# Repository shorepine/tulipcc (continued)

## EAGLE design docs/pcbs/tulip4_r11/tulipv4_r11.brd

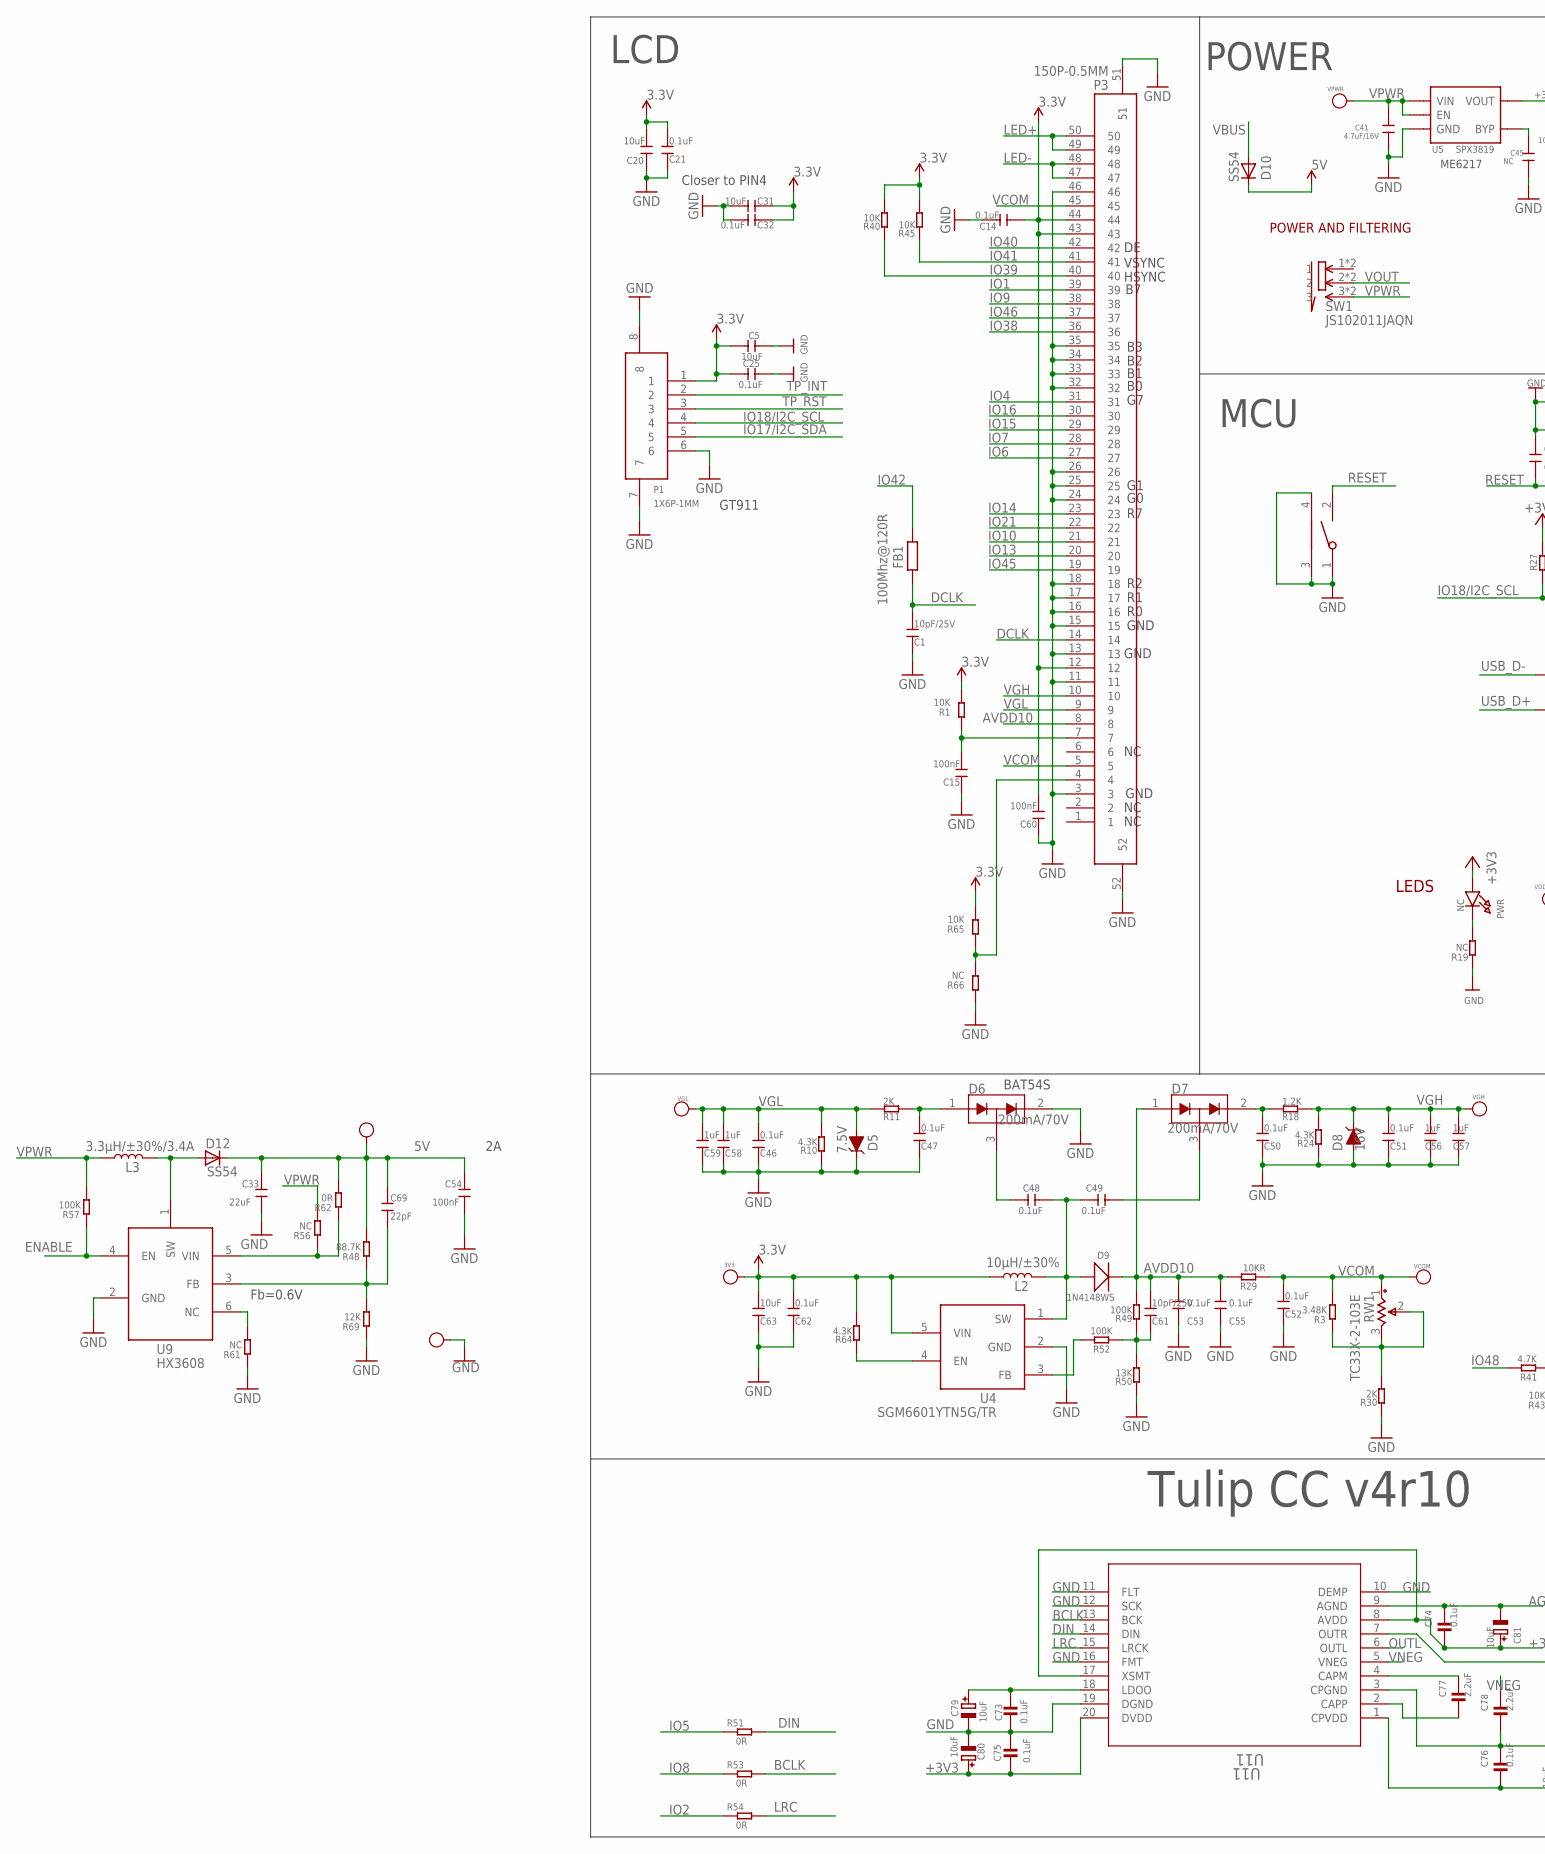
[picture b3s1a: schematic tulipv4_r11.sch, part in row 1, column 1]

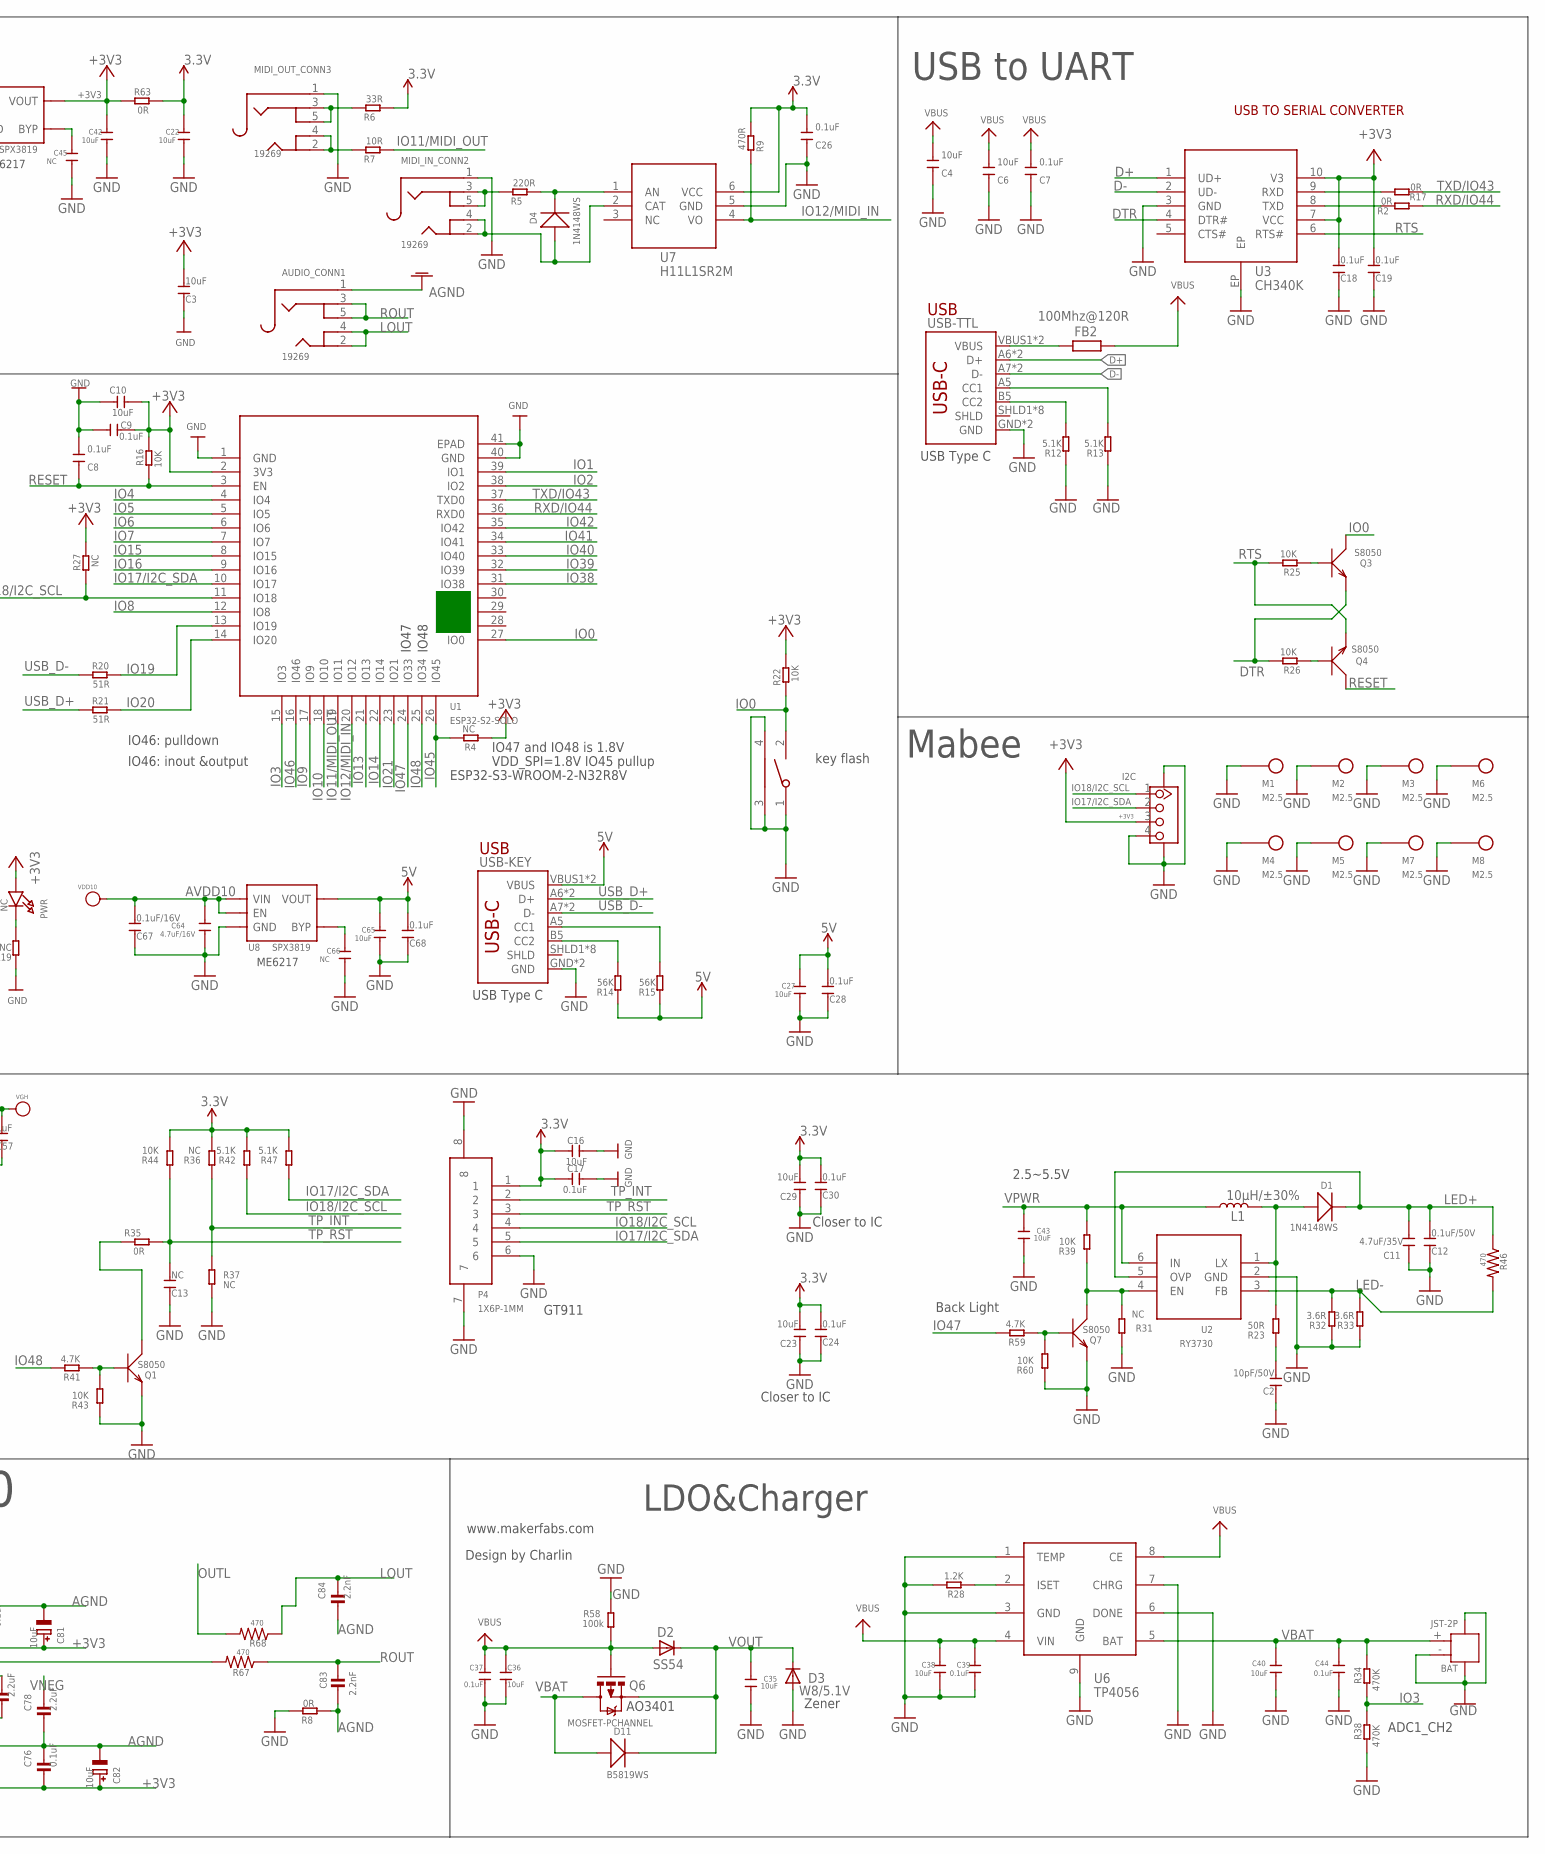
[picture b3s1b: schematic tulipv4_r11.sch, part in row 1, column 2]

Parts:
3V3: PAD-TEST-POINT-CIRCLE'4545'; TP_4545; PARTNO DNP
5V: TEST-POINT'4545'; TP-D45MIL
AUDIO_CONN1: 19269; 4UCONN_19269
BAT: JST-2P; HW2-SMD-2.0-90D
BOOT: TS24CA; 2*4*3.5MM
C1, C61: 10pF/25V; DISCRETE_C0603
C2: 10pF/50V; DISCRETE_C0603
C3, C4, C5, C6, C10, C16, C20, C23, C29, C31, C63: 10uF; DISCRETE_C0603
C7, C8, C9, C14, C17, C18, C19, C21, C24, C25, C26, C28, C30, C32, C46, C47, C48, C49, C50, C51, C52, C53, C55, C62, C68: 0.1uF; DISCRETE_C0603
C11: 4.7uF/35V; DISCRETE_C1206
C12: 0.1uF/50V; DISCRETE_C0603
C13: NC; DISCRETE_C0603
C15, C60: 100nF; DISCRETE_C0603
C22, C27, C35, C36, C38, C40, C42, C43, C65: 10uF; 0603
C33: 22uF; C0603
C37, C39, C44: 0.1uF; 0603
C41, C64: 4.7uF/16V; 0603
C45, C66: NC; 0603
C54: 100nF; C0603
C56, C57, C58, C59: 1uF; DISCRETE_C0603
C67: 0.1uF/16V; DISCRETE_C0603
C69: 22pF; C0603
C73, C74, C75, C76: 0.1uF; 0805-NO@1
C77, C78: 2.2uF; 0805-NO@1
C79, C80, C81, C82: 10uF; PANASONIC_C
C83, C84: 2.2nF; 0805-NO@1
D1, D4, D9: 1N4148WS; SOD323
D2, D10, D12: SS54; DO-214AC
D3: W8/5.1V; SOD123
D5: 7.5V; SOD-323
D6, D7: 200mA/70V; SOT23-3
D8: 16V; SOD-323
D11: B5819WS; SOD323
FB1, FB2: 100Mhz@120R; R0805
GND: TEST-POINT'4545'; TP-D45MIL
I2C: GROVE-CONNECTOR-SMD'90D'; HW4-SMD-2.0-90D
L1, L2: 10µH/±30%; CR54
L3: 3.3µH/±30%/3.4A; CR54
M1, M2, M3, M4, M5, M6, M7, M8: M2.5
MIDI_IN_CONN2: 19269; 4UCONN_19269
MIDI_OUT_CONN3: 19269; 4UCONN_19269
P1, P4: 1X6P-1MM; 1*6P-SMT1MM
P3: 150P-0.5MM; 1*50P-SMT0.5MM
PWR: NC; CHIPLED_0805_NOOUTLINE
Q1, Q3, Q4, Q7: S8050; SOT23
Q6: MOSFET-PCHANNEL; SOT23-3
R1, R39, R40, R43, R44, R45, R60, R65: 10K; DISCRETE_R0603
R2, R17, R35, R51, R53, R54, R63: 0R; R0603
R3: 3.48K; DISCRETE_R0603
R4, R27: NC; R0603
R5: 220R; R0603
R6: 33R; R0603
R7: 10R; R0603
R8, R62: 0R; DISCRETE_R0603
R9: 470R; R0603
R10, R24, R64: 4.3K; DISCRETE_R0603
R11, R30: 2K; DISCRETE_R0603
R12, R13, R42, R47: 5.1K; DISCRETE_R0603
R14, R15: 56K; DISCRETE_R0603
R16, R22, R25, R26: 10K; R0603
R18: 1.2K; DISCRETE_R0603
R19, R31, R36, R37, R56, R61, R66: NC; DISCRETE_R0603
R20, R21: 51R; R0603
R23: 50R; DISCRETE_R0603
R28: 1.2K; R0603
R29: 10KR; DISCRETE_R0603
R32, R33: 3.6R; DISCRETE_R0603
R34, R38: 470K; R0603
R41, R59: 4.7K; DISCRETE_R0603
R46, R67, R68: 470; R0805
R48: 88.7K; DISCRETE_R0603
R49, R52, R57: 100K; DISCRETE_R0603
R50: 13K; DISCRETE_R0603
R58: 100k; R0603
R69: 12K; DISCRETE_R0603
RST: TS24CA; 2*4*3.5MM
RW1: TC33X-2-103E; TC33-3MM-SMD
SW1: JS102011JAQN; SMD-6-2.5MM
U1: ESP32­S2­SOLO; ESP32-­S2-­SOLO
U2: RY3730; SOT23-6
U3: CH340K; ESOP-10-EP-150MIL
U4: SGM6601YTN5G/TR; SOT-23-5
U5, U8: SPX3819; SOT23-5
U6: TP4056; SOP8-1.27P
U7: H11L1SR2M; SOP-6-2.54MM
U9: HX3608; SOT-23-6
U11: U11; PW20_TEX
USB-KEY: USB_C5; USB-C-16P-5
USB-TTL: USB_C5; USB-C-16P-5
VCOM: PAD-TEST-POINT-CIRCLE'4545'; TP_4545
VDD10: PAD-TEST-POINT-CIRCLE'4545'; TP_4545; PARTNO DNP
VGH: PAD-TEST-POINT-CIRCLE'4545'; TP_4545; PARTNO DNP
VGL: PAD-TEST-POINT-CIRCLE'4545'; TP_4545; PARTNO DNP
VPWR: PAD-TEST-POINT-CIRCLE'4545'; TP_4545; PARTNO DNP

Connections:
3.3V: 3V3.T, C5.2, C14.1, C16.2, C17.2, C20.2, C21.2, C22.1, C23.2, C24.2, C25.2, C26.2, C29.2, C30.2, C31.1, C32.1, C60.2, C62.2, C63.2, L2.P$1 (1), P1.1, P3.12, P3.43, P3.44, P4.1, R1.2, R6.1, R9.1, R36.2, R40.2, R42.2, R44.2, R45.2, R47.2, R63.2, R64.2, R65.2, U4.5 (VIN), U7.6 (VCC)
5V: 5V.T, C27.1, C28.2, C33.1, C54.1, C65.1, C68.2, C69.1, D10.C, D12.C, R14.1, R15.1, R48.2, R62.2, U8.5 (VOUT), USB-KEY.VBUS1 (VBUS), USB-KEY.VBUS2 (VBUS)
+3V3: C3.2, C9.1, C10.1, C18.2, C19.2, C42.1, C74.2, C75.2, C76.2, C80.+, C81.+, C82.+, I2C.3, PWR.A, R4.1, R16.2, R22.2, R27.2, R63.1, U1.2 (3V3), U3.7 (VCC), U3.10 (V3), U5.5 (VOUT), U11.1 (CPVDD), U11.8 (AVDD), U11.17 (XSMT), U11.20 (DVDD)
AGND: AUDIO_CONN1.1, C74.1, C76.1, C78.2, C81.-, C82.-, C83.2, C84.2, R8.1, U11.3 (CPGND), U11.9 (AGND)
AVDD10: C53.2, C55.2, C61.2, C64.1, C67.2, D7.1 (A1), D9.-, P3.8, R29.2, R49.2, U8.1 (VIN), U8.3 (EN), VDD10.T
BCLK: R53.2, U11.13 (BCK)
D+: U3.1 (UD+), USB-TTL.A6 (D+), USB-TTL.B6 (D+)
D-: U3.2 (UD-), USB-TTL.A7 (D-), USB-TTL.B7 (D-)
DCLK: C1.2, FB1.1, P3.14
DIN: R51.2, U11.14 (DIN)
DTR: Q3.2 (E), R26.2, U3.4 (DTR#)
ENABLE: R57.1, U9.4 (EN)
GND: BAT.3, BAT.4, BAT.- (2), BOOT.1, BOOT.3, BOOT.4, C1.1, C2.1, C3.1, C4.1, C5.1, C6.1, C7.1, C8.2, C9.2, C10.2, C11.1, C12.1, C13.1, C14.2, C15.1, C16.1, C17.1, C18.1, C19.1, C20.1, C21.1, C22.2, C23.1, C24.1, C25.1, C26.1, C27.2, C28.1, C29.1, C30.1, C31.2, C32.2, C33.2, C35.1, C36.1, C37.2, C38.2, C39.2, C40.2, C41.2, C42.2, C43.1, C44.2, C45.2, C46.1, C47.1, C50.1, C51.1, C52.1, C53.1, C54.2, C55.1, C56.1, C57.1, C58.1, C59.1, C60.1, C62.1, C63.1, C64.2, C65.2, C66.2, C67.1, C68.1, C73.2, C75.1, C79.-, C80.-, D3.A, D5.C, D6.2 (C2), D8.A, GND.T, I2C.4, I2C.SS1, I2C.SS2, M1.1, M2.1, M3.1, M4.1, M5.1, M6.1, M7.1, M8.1, MIDI_IN_CONN2.1, MIDI_OUT_CONN3.1, P1.6, P1.7, P1.8, P3.3, P3.11, P3.13, P3.15, P3.16, P3.17, P3.18, P3.24, P3.25, P3.26, P3.32, P3.33, P3.34, P3.35, P3.46, P3.51, P3.52, P4.6, P4.7, P4.8, Q1.2 (E), Q7.2 (E), R8.2, R10.1, R12.1, R13.1, R19.1, R24.1, R28.2, R30.1, R31.1, R32.1, R33.1, R37.2, R38.1, R43.1, R50.1, R58.2, R60.1, R61.1, R66.1, R69.1, RST.1, RST.3, RST.4, U1.1 (GND), U1.40 (GND), U1.41 (EPAD), U2.2 (GND), U3.3 (GND), U3.EP, U4.2 (GND), U5.2 (GND), U6.1 (TEMP), U6.3 (GND), U6.6 (DONE), U6.7 (CHRG), U6.9 (GND), U7.5 (GND), U8.2 (GND), U9.2 (GND), U11.10 (DEMP), U11.11 (FLT), U11.12 (SCK), U11.16 (FMT), U11.19 (DGND), USB-KEY.GND, USB-KEY.GND2 (GND), USB-TTL.GND, USB-TTL.GND2 (GND)
IO0: BOOT.2, Q3.3 (C), R22.1, U1.27 (IO0)
IO1: P3.39, U1.39 (IO1)
IO2: R54.1, U1.38 (IO2)
IO3: R34.1, R38.2, U1.15 (IO3)
IO4: P3.31, U1.4 (IO4)
IO5: R51.1, U1.5 (IO5)
IO6: P3.27, U1.6 (IO6)
IO7: P3.28, U1.7 (IO7)
IO8: R53.1, U1.12 (IO8)
IO9: P3.38, U1.17 (IO9)
IO10: P3.21, U1.18 (IO10)
IO11/MIDI_OUT: R7.1, U1.19 (IO11)
IO12/MIDI_IN: R9.2, U1.20 (IO12), U7.4 (VO)
IO13: P3.20, U1.21 (IO13)
IO14: P3.23, U1.22 (IO14)
IO15: P3.29, U1.8 (IO15)
IO16: P3.30, U1.9 (IO16)
IO17/I2C_SDA: I2C.2, P1.5, P4.5, R47.1, U1.10 (IO17)
IO18/I2C_SCL: I2C.1, P1.4, P4.4, R27.1, R42.1, U1.11 (IO18)
IO19: R20.2, U1.13 (IO19)
IO20: R21.2, U1.14 (IO20)
IO21: P3.22, U1.23 (IO21)
IO38: P3.36, U1.31 (IO38)
IO39: P3.40, R40.1, U1.32 (IO39)
IO40: P3.42, U1.33 (IO40)
IO41: P3.41, R45.1, U1.34 (IO41)
IO42: FB1.2, U1.35 (IO42)
IO45: P3.19, R4.2, U1.26 (IO45)
IO46: P3.37, U1.16 (IO46)
IO47: R59.2, U1.24 (IO33)
IO48: R41.2, U1.25 (IO34)
LCD_RST: C15.2, P3.7, R1.1
LED+: C11.2, C12.2, D1.-, P3.49, P3.50, R46.1, U2.5 (OVP)
LED-: P3.47, P3.48, R32.2, R33.2, R46.2, U2.3 (FB)
LOUT: AUDIO_CONN1.2, AUDIO_CONN1.4, C84.1, R68.1
LRC: R54.2, U11.15 (LRCK)
unnamed: C47.2, D6.1 (A1), R11.1
unnamed: Q4.1 (B), R26.1
unnamed: Q3.1 (B), R25.1
unnamed: C61.1, R49.1, R50.2, R52.1
unnamed: P3.4, R65.1, R66.2
unnamed: R15.2, USB-KEY.A5 (CC1)
unnamed: PWR.C, R19.2
unnamed: C48.2, D6.3 (COM)
unnamed: C48.1, C49.2, D9.+, L2.P$2 (2), U4.1 (SW)
unnamed: R13.2, USB-TTL.A5 (CC1)
unnamed: R12.2, USB-TTL.B5 (CC2)
unnamed: C49.1, D7.3 (COM)
unnamed: C50.2, D7.2 (C2), R18.2
unnamed: R14.2, USB-KEY.B5 (CC2)
unnamed: R52.2, U4.3 (FB)
unnamed: R3.1, R30.2, RW1.2, RW1.3
unnamed: D1.+, L1.P$2 (2), R23.2, U2.1 (LX)
unnamed: Q1.3 (C), R35.1
unnamed: R64.1, U4.4 (EN)
unnamed: Q1.1 (B), R41.1, R43.2
unnamed: FB2.1, USB-TTL.VBUS1 (VBUS), USB-TTL.VBUS2 (VBUS)
unnamed: C2.2, R23.1
unnamed: MIDI_IN_CONN2.3, MIDI_IN_CONN2.5, R5.2
unnamed: Q7.3 (C), R31.2, R39.1, U2.4 (EN)
unnamed: D12.A, L3.P$2 (2), U9.1 (SW)
unnamed: D4.-, R5.1, U7.1 (AN)
unnamed: MIDI_OUT_CONN3.3, MIDI_OUT_CONN3.5, R6.2
unnamed: C69.2, R48.1, R69.2, U9.3 (FB)
unnamed: Q7.1 (B), R59.1, R60.2
unnamed: R28.1, U6.2 (ISET)
unnamed: R61.2, U9.6 (NC)
unnamed: R56.1, R62.1, U9.5 (VIN)
unnamed: C66.1, U8.4 (BYP)
unnamed: MIDI_OUT_CONN3.2, MIDI_OUT_CONN3.4, R7.2
unnamed: D4.+, MIDI_IN_CONN2.2, MIDI_IN_CONN2.4, U7.2 (CAT)
unnamed: C73.1, C79.+, U11.18 (LDOO)
unnamed: R67.2, U11.7 (OUTR)
unnamed: C77.1, U11.4 (CAPM)
unnamed: R17.2, U3.9 (RXD)
unnamed: C77.2, U11.2 (CAPP)
unnamed: R2.2, U3.8 (TXD)
unnamed: C45.1, U5.4 (BYP)
OUTL: R68.2, U11.6 (OUTL)
RESET: C8.1, Q4.3 (C), R16.1, RST.2, U1.3 (EN)
ROUT: AUDIO_CONN1.3, AUDIO_CONN1.5, C83.1, R67.1
RTS: Q4.2 (E), R25.2, U3.6 (RTS#)
RXD/IO44: R2.1, U1.36 (RXD0)
TP_INT: P1.2, P4.2, R36.1, R37.1
TP_RST: C13.2, P1.3, P4.3, R35.2, R44.1
TXD/IO43: R17.1, U1.37 (TXD0)
USB_D+: R21.1, USB-KEY.A6 (D+), USB-KEY.B6 (D+)
USB_D-: R20.1, USB-KEY.A7 (D-), USB-KEY.B7 (D-)
VBAT: BAT.+ (1), C40.1, C44.1, D11.+, Q6.3 (D), R34.2, U6.5 (BAT)
VBUS: C4.2, C6.2, C7.2, C36.2, C37.1, C38.1, C39.1, D2.A, D10.A, FB2.2, Q6.1 (G), R58.1, U6.4 (VIN), U6.8 (CE)
VCOM: C52.2, P3.5, P3.45, R3.2, R29.1, RW1.1, VCOM.T
VGH: C51.2, C56.2, C57.2, D8.C, P3.10, R18.1, R24.2, VGH.T
VGL: C46.2, C58.2, C59.2, D5.A, P3.9, R10.2, R11.2, VGL.T
VNEG: C78.1, U11.5 (VNEG)
VOUT: C35.2, D2.C, D3.C, D11.-, Q6.2 (S), SW1.2, SW1.2@1 (2)
VPWR: C41.1, C43.2, L1.P$1 (1), L3.P$1 (1), R39.2, R56.2, R57.2, SW1.3, SW1.3@1 (3), U2.6 (IN), U5.1 (VIN), U5.3 (EN), VPWR.T

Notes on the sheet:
www.makerfabs.com
Design by Charlin
USB
LEDS
POWER AND FILTERING
USB TO SERIAL CONVERTER
Tulip CC v4r10
POWER
USB to UART
USB Type C
GT911
Closer to IC
Back Light
IO46: pulldown
IO46: inout &output
Mabee
LCD
MCU
ESP32-S3-WROOM-2-N32R8V
IO47
IO48
Closer to PIN4
LDO&Charger
AO3401
ME6217
VSYNC
HSYNC
GND
BAT54S
key flash
2.5~5.5V
Zener
IO47 and IO48 is 1.8V
VDD_SPI=1.8V IO45 pullup
ADC1_CH2
Fb=0.6V

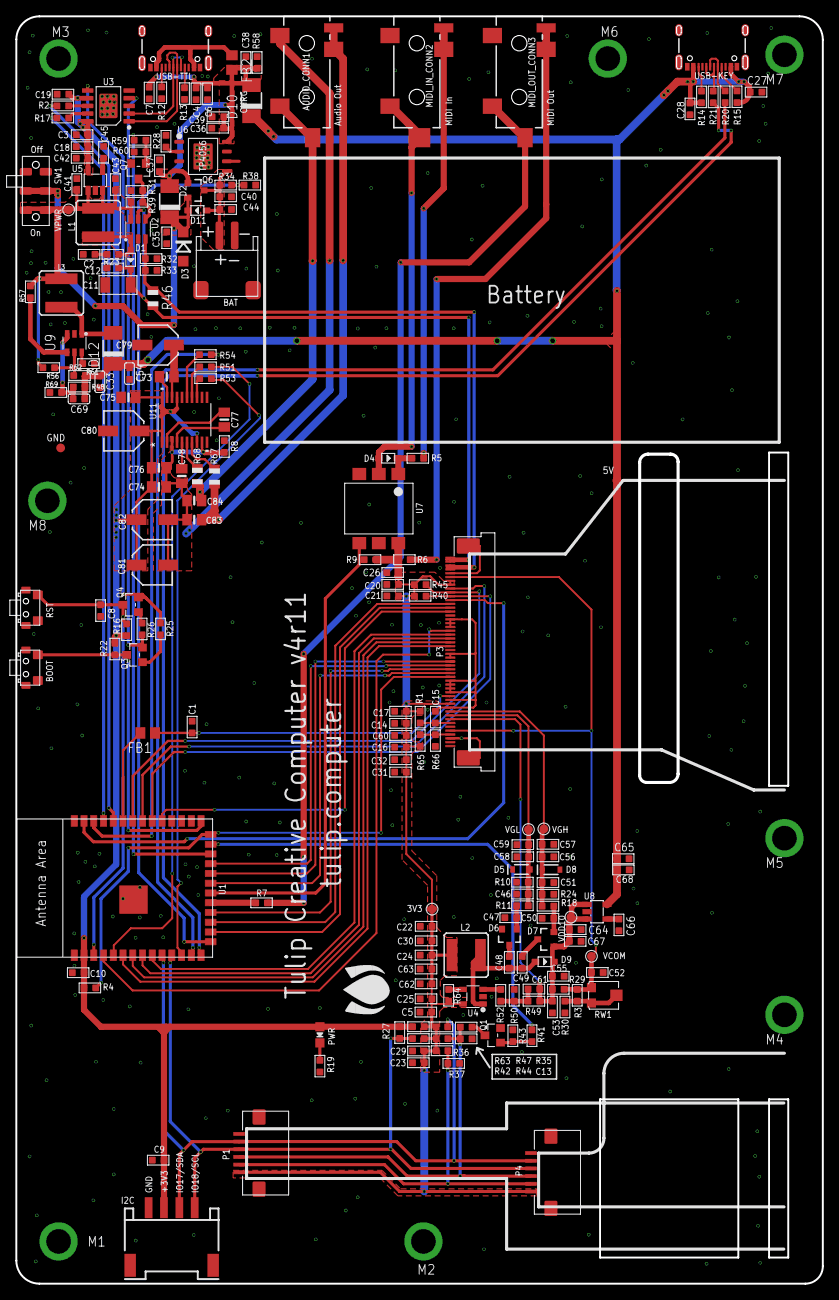
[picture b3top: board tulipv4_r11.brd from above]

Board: 2 copper layers, 105.0 x 165.0 mm, 211 parts (0 on the bottom side), 109 nets.

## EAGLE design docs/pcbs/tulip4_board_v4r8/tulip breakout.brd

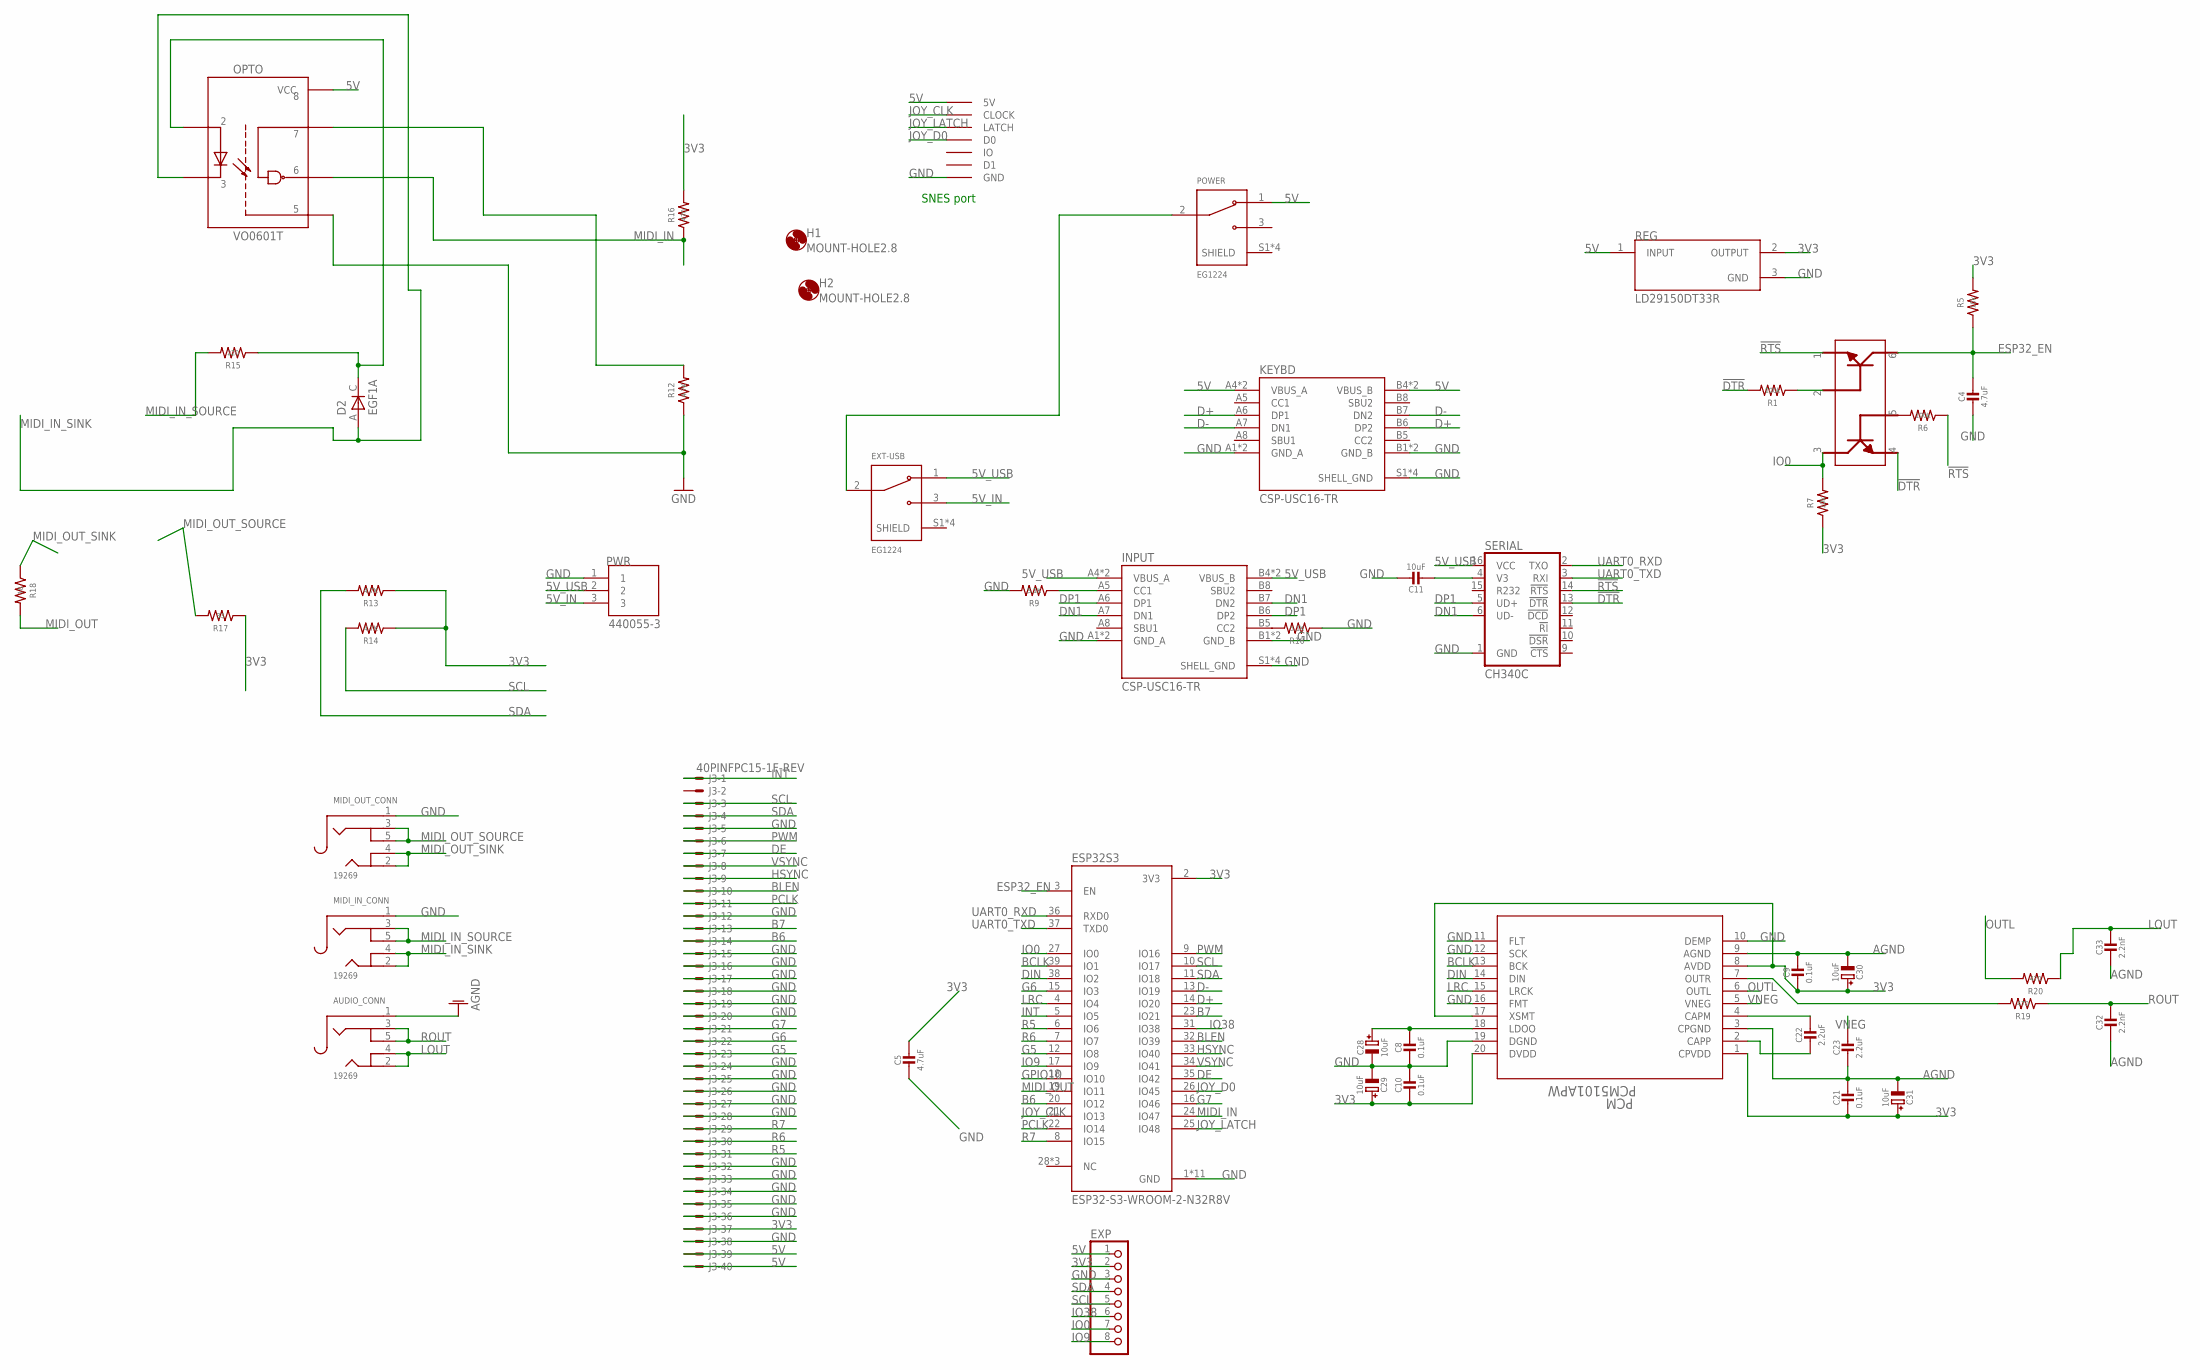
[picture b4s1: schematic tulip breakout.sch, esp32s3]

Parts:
AUDIO_CONN: 19269; 4UCONN_19269
C4, C5: 4.7uF; 0805-NO
C8, C9, C10, C21: 0.1uF; 0805-NO
C11: 10uF; 0805-NO
C22, C23: 2.2uF; 0805-NO
C28, C29, C30, C31: 10uF; PANASONIC_C
C32, C33: 2.2nF; 0805-NO
D2: EGF1A; DIOM449X264X300L114X135N
ESP32S3: ESP32-S3-WROOM-2-N32R8V; XCVR_ESP32-S3-WROOM-2-N32R8V
EXP: PINHD-1X8BIG; 1X08-BIG
EXT-USB: EG1224; SW_EG1224
H1, H2: MOUNT-HOLE2.8; 2,8
INPUT: CSP-USC16-TR; VALCON_CSP-USC16-TR
J3: 40PINFPC15-1F-REV; XF2M-4015-1F-REVERSE
KEYBD: CSP-USC16-TR; VALCON_CSP-USC16-TR
MIDI_IN_CONN: 19269; 4UCONN_19269
MIDI_OUT_CONN: 19269; 4UCONN_19269
OPTO: VO0601T; SOIC127P610X331-8N
PCM: PCM5101APW; PW20_TEX
POWER: EG1224; SW_EG1224
PWR: 440055-3; TE_440055-3
R1, R6: 100k; R0805
R5, R7: 10k; R0805
R9, R10: 5.1K; R0805
R12, R13, R14: 4.7K; R0805
R15: 220; R0805
R16, R19, R20: 470; R0805
R17: 33; R0805
R18: 10; R0805
REG: LD29150DT33R; DPAK456P972X240-3N
RESET: MBT3904DW1T1G; SOT236
SERIAL: CH340C; SO016
SNES: SNESCONN

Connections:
3V3: C5.1, C9.2, C10.2, C21.2, C29.+, C30.+, C31.+, ESP32S3.2 (3V3), EXP.2, J3.37 (MS), PCM.1 (CPVDD), PCM.8 (AVDD), PCM.17 (XSMT), PCM.20 (DVDD), R5.2, R7.1, R13.1, R14.1, R16.2, R17.1, REG.2 (OUTPUT)
5V: EXP.1, J3.39 (MS), J3.40 (MS), KEYBD.A4 (VBUS_A), KEYBD.A9 (VBUS_A), KEYBD.B4 (VBUS_B), KEYBD.B9 (VBUS_B), OPTO.8 (VCC), POWER.1, REG.1 (INPUT), SNES.5V
5V_IN: EXT-USB.3, PWR.3
5V_USB: EXT-USB.1, INPUT.A4 (VBUS_A), INPUT.A9 (VBUS_A), INPUT.B4 (VBUS_B), INPUT.B9 (VBUS_B), PWR.2, SERIAL.16 (VCC)
!DTR: R1.2, RESET.4, SERIAL.13 (!DTR)
!RTS: R6.1, RESET.1, SERIAL.14 (!RTS)
AGND: AUDIO_CONN.1, C9.1, C21.1, C23.2, C30.-, C31.-, C32.2, C33.2, PCM.3 (CPGND), PCM.9 (AGND)
B6: ESP32S3.20 (IO12), J3.14 (MS)
B7: ESP32S3.23 (IO21), J3.13 (MS)
BCLK: ESP32S3.39 (IO1), PCM.13 (BCK)
BLEN: ESP32S3.32 (IO39), J3.10 (MS)
D+: ESP32S3.14 (IO20), KEYBD.A6 (DP1), KEYBD.B6 (DP2)
D-: ESP32S3.13 (IO19), KEYBD.A7 (DN1), KEYBD.B7 (DN2)
DE: ESP32S3.35 (IO42), J3.7 (MS)
DIN: ESP32S3.38 (IO2), PCM.14 (DIN)
DN1: INPUT.A7 (DN1), INPUT.B7 (DN2), SERIAL.6 (UD-)
DP1: INPUT.A6 (DP1), INPUT.B6 (DP2), SERIAL.5 (UD+)
ESP32_EN: C4.1, ESP32S3.3 (EN), R5.1, RESET.6
EXT-USB: EXT-USB.2, POWER.2
G5: ESP32S3.12 (IO8), J3.23 (MS)
G6: ESP32S3.15 (IO3), J3.22 (MS)
G7: ESP32S3.16 (IO46), J3.21 (MS)
GND: C4.2, C5.2, C8.2, C10.1, C11.1, C28.-, C29.-, ESP32S3.1 (GND), ESP32S3.40 (GND), ESP32S3.41_1 (GND), ESP32S3.41_2 (GND), ESP32S3.41_3 (GND), ESP32S3.41_4 (GND), ESP32S3.41_5 (GND), ESP32S3.41_6 (GND), ESP32S3.41_7 (GND), ESP32S3.41_8 (GND), ESP32S3.41_9 (GND), EXP.3, INPUT.A1 (GND_A), INPUT.A12 (GND_A), INPUT.B1 (GND_B), INPUT.B12 (GND_B), INPUT.S1 (SHELL_GND), INPUT.S2 (SHELL_GND), INPUT.S3 (SHELL_GND), INPUT.S4 (SHELL_GND), J3.5 (MS), J3.12 (MS), J3.15 (MS), J3.16 (MS), J3.17 (MS), J3.18 (MS), J3.19 (MS), J3.20 (MS), J3.24 (MS), J3.25 (MS), J3.26 (MS), J3.27 (MS), J3.28 (MS), J3.32 (MS), J3.33 (MS), J3.34 (MS), J3.35 (MS), J3.36 (MS), J3.38 (MS), KEYBD.A1 (GND_A), KEYBD.A12 (GND_A), KEYBD.B1 (GND_B), KEYBD.B12 (GND_B), KEYBD.S1 (SHELL_GND), KEYBD.S2 (SHELL_GND), KEYBD.S3 (SHELL_GND), KEYBD.S4 (SHELL_GND), MIDI_IN_CONN.1, MIDI_OUT_CONN.1, OPTO.5 (GND), PCM.10 (DEMP), PCM.11 (FLT), PCM.12 (SCK), PCM.16 (FMT), PCM.19 (DGND), PWR.1, R9.2, R10.1, R12.1, REG.3 (GND), SERIAL.1 (GND), SNES.GND
GPIO10: ESP32S3.18 (IO10)
HSYNC: ESP32S3.33 (IO40), J3.9 (MS)
INT: ESP32S3.5 (IO5), J3.1 (MSV)
IO0: ESP32S3.27 (IO0), EXP.7, R7.2, RESET.3
IO9: ESP32S3.17 (IO9), EXP.8
IO38: ESP32S3.31 (IO38), EXP.6
JOY_CLK: ESP32S3.21 (IO13), SNES.CLOCK
JOY_D0: ESP32S3.26 (IO45), SNES.D0
JOY_LATCH: ESP32S3.25 (IO48), SNES.LATCH
LOUT: AUDIO_CONN.2, AUDIO_CONN.4, C33.1, R20.1
LRC: ESP32S3.4 (IO4), PCM.15 (LRCK)
MIDI_IN: ESP32S3.24 (IO47), OPTO.6 (VO), R16.1
MIDI_IN_SINK: D2.A, MIDI_IN_CONN.2, MIDI_IN_CONN.4, OPTO.3 (C)
MIDI_IN_SOURCE: MIDI_IN_CONN.3, MIDI_IN_CONN.5, R15.2
MIDI_OUT: ESP32S3.19 (IO11), R18.2
MIDI_OUT_SINK: MIDI_OUT_CONN.2, MIDI_OUT_CONN.4, R18.1
MIDI_OUT_SOURCE: MIDI_OUT_CONN.3, MIDI_OUT_CONN.5, R17.2
unnamed: R1.1, RESET.2
unnamed: R6.2, RESET.5
unnamed: INPUT.B5 (CC2), R10.2
unnamed: C8.1, C28.+, PCM.18 (LDOO)
unnamed: PCM.7 (OUTR), R19.2
unnamed: C22.1, PCM.4 (CAPM)
unnamed: C22.2, PCM.2 (CAPP)
unnamed: D2.C, OPTO.2 (A), R15.1
unnamed: OPTO.7 (VE), R12.2
unnamed: C11.2, SERIAL.4 (V3)
unnamed: INPUT.A5 (CC1), R9.1
OUTL: PCM.6 (OUTL), R20.2
PCLK: ESP32S3.22 (IO14), J3.11 (MS)
PWM: ESP32S3.9 (IO16), J3.6 (MS)
R5: ESP32S3.6 (IO6), J3.31 (MS)
R6: ESP32S3.7 (IO7), J3.30 (MS)
R7: ESP32S3.8 (IO15), J3.29 (MS)
ROUT: AUDIO_CONN.3, AUDIO_CONN.5, C32.1, R19.1
SCL: ESP32S3.10 (IO17), EXP.5, J3.3 (MS), R14.2
SDA: ESP32S3.11 (IO18), EXP.4, J3.4 (MS), R13.2
UART0_RXD: ESP32S3.36 (RXD0), SERIAL.2 (TXO)
UART0_TXD: ESP32S3.37 (TXD0), SERIAL.3 (RXI)
VNEG: C23.1, PCM.5 (VNEG)
VSYNC: ESP32S3.34 (IO41), J3.8 (MS)

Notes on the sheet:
SNES port

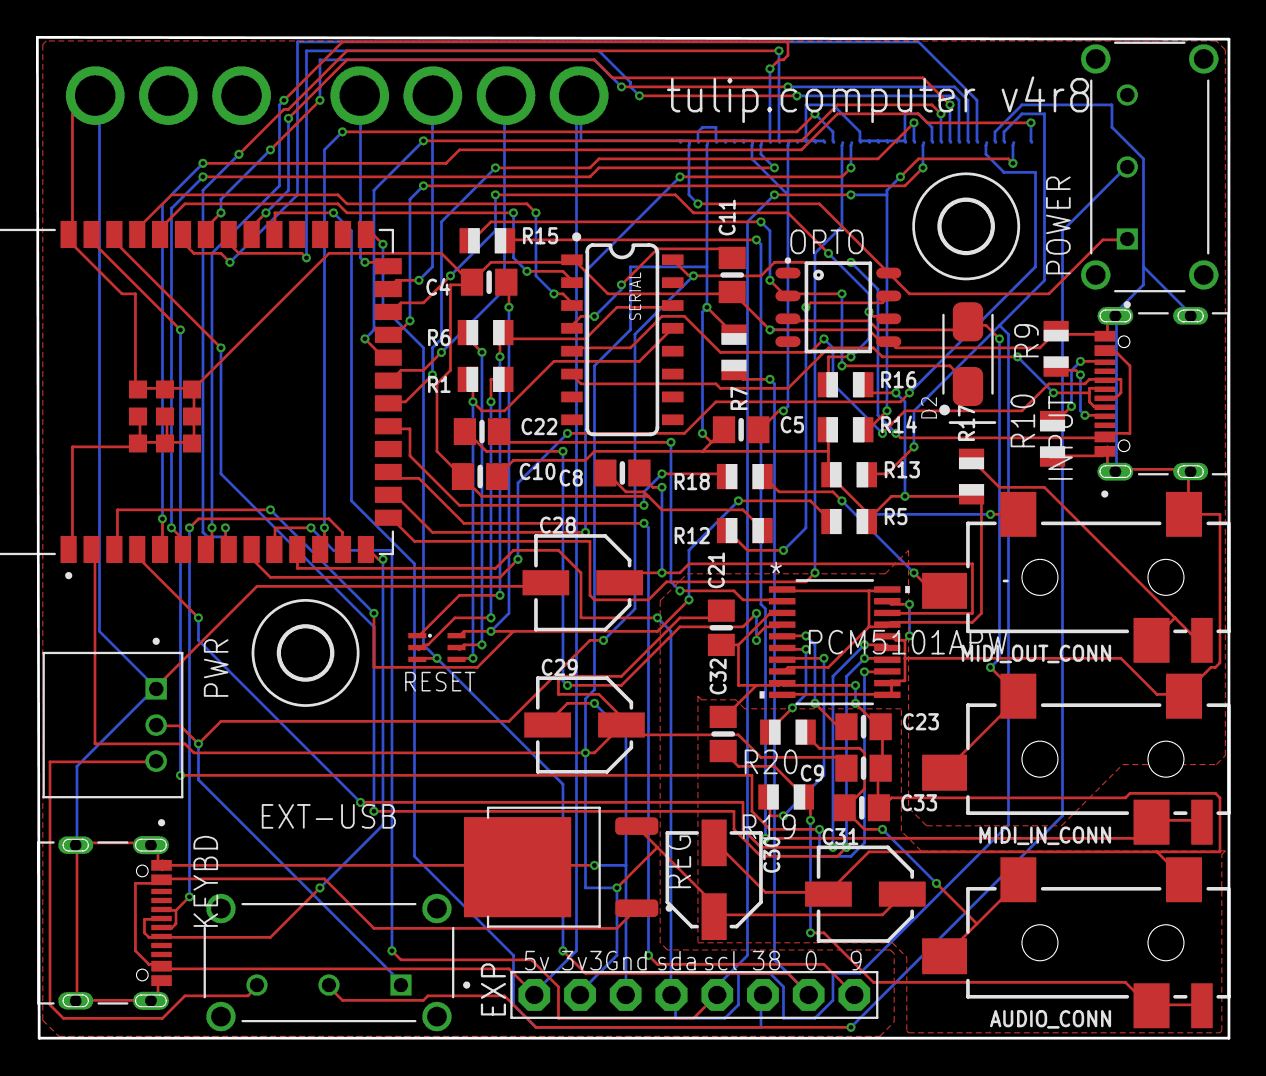
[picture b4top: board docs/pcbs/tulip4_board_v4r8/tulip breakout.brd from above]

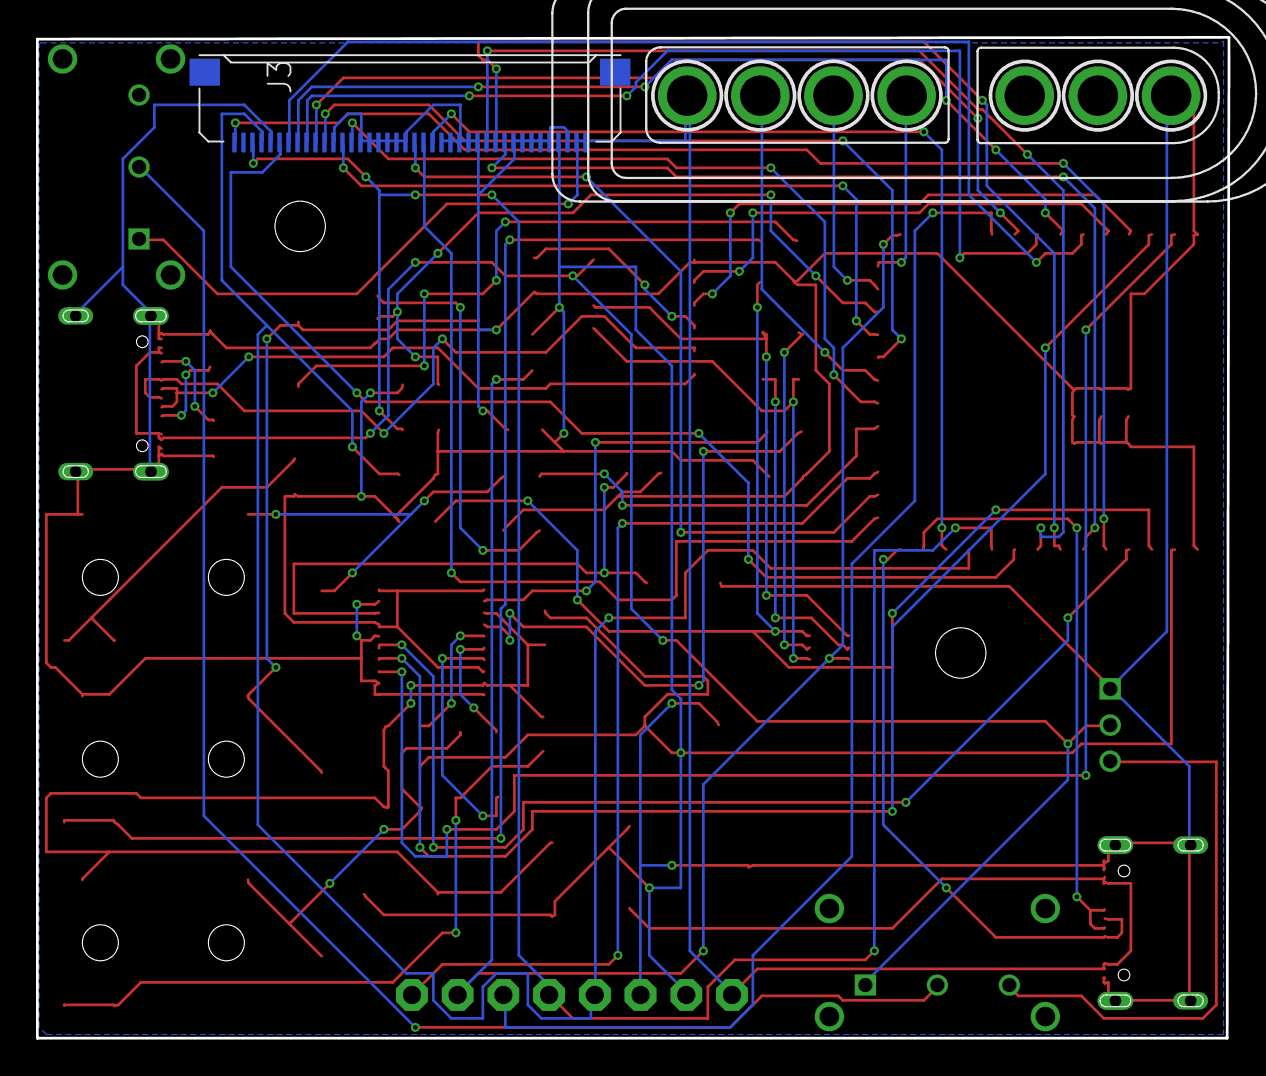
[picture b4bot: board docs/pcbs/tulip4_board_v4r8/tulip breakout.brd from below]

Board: 2 copper layers, 66.2 x 55.6 mm, 50 parts (2 on the bottom side), 63 nets.

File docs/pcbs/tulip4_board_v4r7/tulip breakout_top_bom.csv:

Comment,Designator,Footprint,LCSC Part #
0.1uF,C8 C9 C10 C21,0805-NO,
2.2nF,C32 C33,0805-NO,
2.2uF,C22 C23,0805-NO,
4.7K,R12 R13 R14,R0805,
4.7uF,C4 C5,0805-NO,
5.1K,R9 R10,R0805,
6N137S,6N137S,8-SMD,
10,R18,R0805,
10k,R5 R7,R0805,
10uF,C11,0805-NO,
10uF,C28 C29 C30 C31,PANASONIC_C,
33,R17,R0805,
100k,R1 R6,R0805,
220,R15,R0805,
470,R16 R19 R20,R0805,
500ASSP1SM6QE,POWER,SW_500ASSP1SM6QE,
19269,AUDIO_CONN MIDI_IN_CONN MIDI_OUT_CONN,4UCONN_19269,
CH340C,U6,SO016,
CSP-USC16-TR,J1,VALCON_CSP-USC16-TR,
EGF1A,D2,DIOM449X264X300L114X135N,
ESP32-S3-WROOM-2-N32R8V,U1,XCVR_ESP32-S3-WROOM-2-N32R8V,
FH12-40S-0.5SH,X2,FH12-40S-0.5SH,
LD29150DT33R,U2,DPAK456P972X240-3N,
MBT3904DW1T1G,RESET,SOT236,
PCM5101APW,U3,PW20_TEX,
TSM-106-02-L-DH-A,J3,SAMTEC_TSM-106-02-L-DH-A,
USB-A-S-X-X-SM2,USBKB,SAMTEC_USB-A-S-X-X-SM2,
